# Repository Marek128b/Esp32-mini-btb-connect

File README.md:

# Esp32-mini-btb-connect V1.1

**table of content**
- [Esp32-mini-btb-connect V1.1](#esp32-mini-btb-connect-v11)
  - [Debugging Prozess](#debugging-prozess)
    - [Debugging Checklist](#debugging-checklist)
    - [Debugging Protocol](#debugging-protocol)
  - [Description](#description)
  - [Schematic](#schematic)
    - [Power-Circuit Description](#power-circuit-description)
  - [PCB](#pcb)
    - [3D-Layout](#3d-layout)
    - [Bottom-PCB Description](#bottom-pcb-description)
    - [Pinout](#pinout)

## Debugging Prozess
### Debugging Checklist
- [x] checking chip working crystal oszillator
- [x] checking voltage converter 5V - 3V3
- [x] checking power supply
- [x] checking usb to serial CH340E
- [ ] testing uploading
- [ ] testing WiFi and Bluetooth
- [x] testing on board LEDs PWM WS2812
- [ ] testing battery charcher 

### Debugging Protocol
**31.01.2023:**
I got the First Blink Programm uploaded with an external USB to UART adapter an external Power using an AMS1117-3.3 and electrolytic capasitors. The First Problem i got was that the VS-Code with the PlatformIO plugin didn't recognize the denky_d4-ESP32-pico-V3-02 module. To fix that i had to reinstall the Espressif 32 boards from the Platforms tab, i just hit uninstall on the Espressif 32 and went to the EMBEDDED tab to search for the Espressif 32 and click install. And that fixed the Problem. The next Problem was that the Programming didn't work but that was due to a design error in the first version design of this product. i fixed that by connecting on the back side of the board the CN2 connector pins IO32 and IO33 to a 40MHz crystal and two load capacitors with a value of 12pF and a pin of the crystal to ground. <br>

**02.02.2023:**
I got the linear Dropout Regulator working now, the Error was that on the board the EN Pin was tied to GND istead of VCC (5V). This would have never aktivated the Regulator. BYP- Capacitor not strictly needed for operation but it's better to have a small 10nF capacitor connected to it and Ground. <br>

**18.02.2023:**
The led test programm got uploaded using an FTDI usb to serial adapter. this also worked without the 40Mhz crystal because the esp32-pico-v3-02 chip is a SoC and therefor doesn't need an external crystal to work so i just cut the wires to the crystal. The usb uart wires had to be resoldered as they got lose and the programm wouldn't upload anymore. I wrote a tiny library for the esp which makes working without the delay() function easier. <br>

**26.03.2023:**
After designing a CH340E usb to serial board and soldering all component's consisting of a CH340E, two capacitors, two LEDs and resistors I tested the Board and it worked, but i didn't design it quite right so I had to solder two realy small wires to the pin 4 and 5 of the CH340 I made a mistake and accidentily soldered the pin 4 to ground. After connecting the board via USB Windows detected the Board as a "USB Serial" board but not as a COM Port Serial.

**29.03.2023**
After designing the new USB-C board for the CH340E which didn't work because i havn't designed the board right. Now i am going to design a USB-C board and test the board with some jumper Wires and a breadboard so i can further see what i designed wrong and after that i am going to design the USB-C board with the CH340E again.

___

## Description
With this project you are able to connect one Esp32 microcontroller with internal 8MB FLASH and 2MB SRAM to any project you would like. This PCB has two onboard Buttons for Boot-mode and Resetting. It has two Power LEDs and one LED on GPIO2. It also has an adressable WS2812 RGB LED on GPIO5. The board has a 2.4GHz onboard antenna as well as an external antenna connector that can be switched between by setting one or the other GPIO to HIGH. This Project has a circuit for charching a LiPo/LiIon Battery and automatically switching between Battery and USB power.
___

## Schematic

### Power-Circuit Description
The power get's switched automatically using the N-Channnel MOSFET (Q3). The gate of the MOSFET gets normally pulled Low via a 10k Ohm resistor. If there is no USB voltage (+5V) the MOSFET switches the power so that the Battery Voltage (Vbat) can pass through to the Voltage Regulator which regulates it's output voltage to 3V3. If however USB Voltage (+5V) is present the MOSFET switches off and the USB Voltage goes through the Diode (D1) and proceedes to go to the Voltage Regulator.
___

## PCB

### 3D-Layout

### Bottom-PCB Description
The Bottom side of the PCB has 4 slim Board to Board connector's which transport USB power, 3V3 regulated voltage as well as Digital ans Analog Pin functions to any daughter board. There are some extra 1mm pads to quickly test and Programm this Mainboard using a special made programmer and test-software.

### Pinout

CN1|Pin Nr.|GPIO|Function|
|--|-------|----|--------|
|   |1|IO14| H_SCK|
|   |2|IO12|H_MISO|
|   |3|IO13|H_MOSI|
|   |4|**3V3**|**POWER**|
|   |5|**+5V**|**POWER**|
|   |6|IO4|
|   |7|IO0|
|   |8|IO2|
|   |9|IO15|H_CS|
|   |10|**GND**|**Power**|

CN2|Pin Nr.|GPIO|Function|
|--|-------|----|--------|
|   |1|IO15|
|   |2|I36|Input only|
|   |3|I37|Input only|
|   |4|**3V3**|**POWER**|
|   |5|**+5V**|**POWER**|
|   |6|IO26|
|   |7|IO27|
|   |8|IO34|
|   |9|IO35|
|   |10|**GND**|**POWER**|

CN3|Pin Nr.|GPIO|Function|
|--|-------|----|--------|
|  |1      |IO21|SDA|
|  |2      |IO1|TX|
|  |3      |IO3|RX|
|  |4      |IO33|
|  |5      |IO22|SCL|
|  |6      |IO19|
|  |7      |I38|Input only|
|  |8      |I39|Input only|
|  |9      |EN | EN|
|  |10     |**GND**|**POWER**|

CN4|Pin Nr.|GPIO|Function|
|--|-------|----|--------|
|   |1|IO11|
|   |2|IO10|
|   |3|IO9|
|   |4|IO32|
|   |5|IO20|
|   |6|IO5|
|   |7|IO8|
|   |8|IO7|
|   |9|IO6|
|   |10|**GND**|**POWER**|

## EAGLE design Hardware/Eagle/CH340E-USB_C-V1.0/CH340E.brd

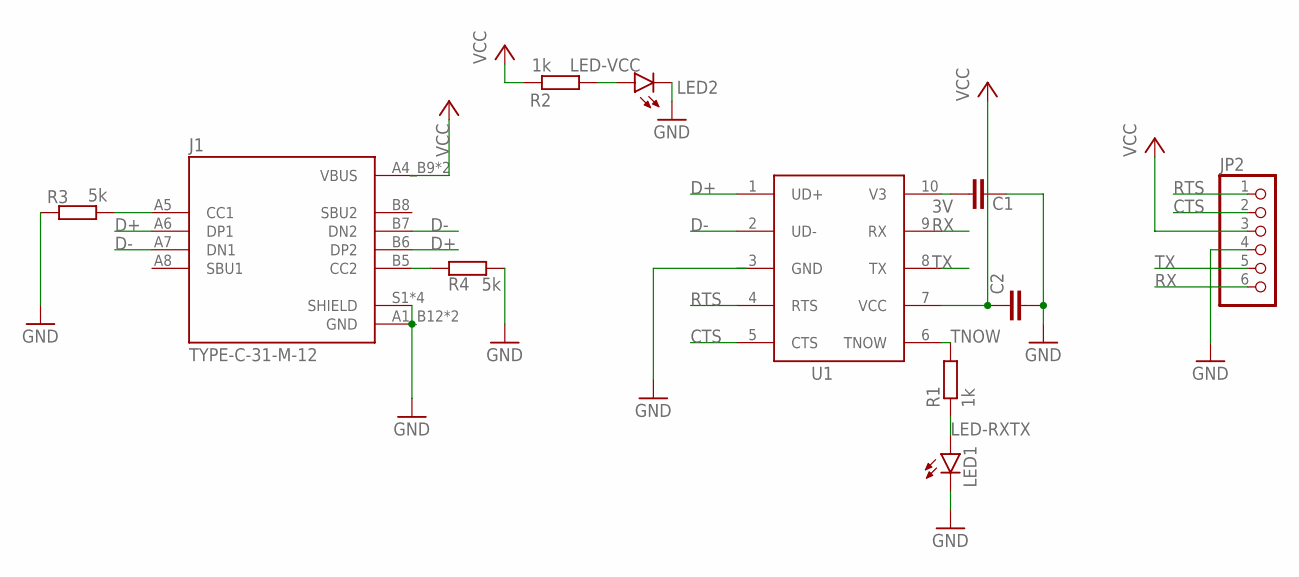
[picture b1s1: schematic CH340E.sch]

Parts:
C1, C2: C-EUC0603; C0603
J1: TYPE-C-31-M-12; HRO_TYPE-C-31-M-12
JP2: PINHD-1X6; 1X06
LED1, LED2: LEDCHIPLED_0603; CHIPLED_0603
R1, R2: 1k; R0603
R3, R4: 5k; R0603
U1: CH340ESMD; MSOP10

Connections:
3V: C1.1, U1.10 (V3)
CTS: JP2.2, U1.5 (CTS)
D+: J1.A6 (DP1), J1.B6 (DP2), U1.1 (UD+)
D-: J1.A7 (DN1), J1.B7 (DN2), U1.2 (UD-)
GND: C1.2, C2.2, J1.A1_B12 (GND), J1.B1_A12 (GND), J1.S1 (SHIELD), J1.S2 (SHIELD), J1.S3 (SHIELD), J1.S4 (SHIELD), JP2.4, LED1.C, LED2.C, R3.2, R4.1, U1.3 (GND)
LED-RXTX: LED1.A, R1.1
LED-VCC: LED2.A, R2.1
unnamed: J1.A5 (CC1), R3.1
unnamed: J1.B5 (CC2), R4.2
RTS: JP2.1, U1.4 (RTS)
RX: JP2.6, U1.9 (RX)
TNOW: R1.2, U1.6 (TNOW)
TX: JP2.5, U1.8 (TX)
VCC: C2.1, J1.A4_B9 (VBUS), J1.B4_A9 (VBUS), JP2.3, R2.2, U1.7 (VCC)

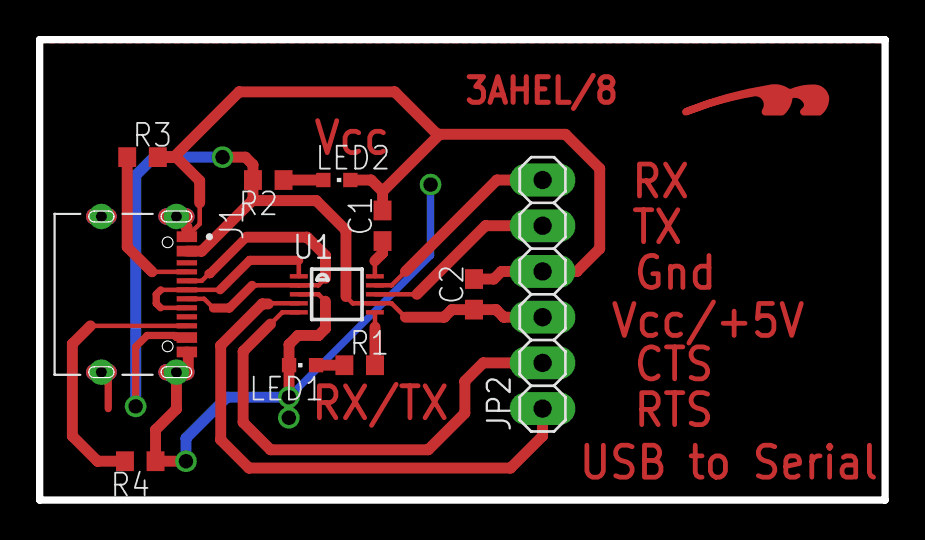
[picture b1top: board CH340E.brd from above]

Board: 2 copper layers, 47.0 x 25.6 mm, 12 parts (0 on the bottom side), 14 nets.

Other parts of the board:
U$2: LOGOTOP_8

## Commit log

2022-12-20 basic structure 1
2022-12-20 better BOM readme
2022-12-21 added 3d layout
2022-12-22 added description
2023-01-31 work process of 31.01.2023 fixing and debugging
2023-02-02 added checklist for debugging
2023-02-11 Added debugging information for 3V3
2023-02-19 added test code for leds
2023-02-19 added code
2023-02-19 changed name
2023-02-19 added protocol of 18.02.2023
2023-02-20 added picture
2023-02-21 added screenshot
2023-02-21 changed code to fade led on and off
2023-02-21 added getInterval function
2023-02-21 added rgb fade
2023-03-07 added and moved images PCB
2023-03-07 added V1.1 pictures and Pinout
2023-03-07 added PCB and Schematic pictures
2023-03-09 Add descriptions for Bottom Pcb and Power circuit
2023-03-27 added ch340E description
2023-03-30 added eagle files, libraries and CH340E-USBC V1
